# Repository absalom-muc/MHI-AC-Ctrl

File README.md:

# MHI-AC-Ctrl
Reads and writes data (e.g. power, mode, fan status etc.) from/to a Mitsubishi Heavy Industries (MHI) air conditioner (AC) via SPI controlled by MQTT. The AC is the SPI master and the ESP8266 is the SPI slave.

# Attention:
:warning: You have to open the indoor unit to have access to the SPI. Opening of the indoor unit should be done by 
a qualified professional because faulty handling may cause leakage of water, electric shock or fire! :warning: 

# Prerequisites:
For use of the program you have to connect your ESP8266 (I use a LOLIN(WEMOS) D1 R2 & mini with 80 MHz) via a
cable connector to your air conditioner. This has to be a split device (separated indoor and outdoor unit).
I assume that all AC units of the type "SRK xx ZS-S" / "SRC xx ZS-S" are supported. I use the indoor unit SRK 35 ZS-S and the outdoor unit SRC 35 ZS-S. Users reported that additionally the following models are supported:

- [SRF xx ZJX-S1](https://github.com/absalom-muc/MHI-AC-Ctrl/issues/17#issue-632187165)
- [SRF xx ZMX-S](https://github.com/absalom-muc/MHI-AC-Ctrl/issues/17#issuecomment-704789297)
- [SRF xx ZMXA-S](https://github.com/absalom-muc/MHI-AC-Ctrl/pull/91)
- SRF xx ZF-W
- [SRF xx ZS-W](https://github.com/absalom-muc/MHI-AC-Ctrl/pull/216#issue-3234769567) works with frame size 20
- [SRK xx ZJ-S](https://github.com/absalom-muc/MHI-AC-Ctrl/issues/10)
- [SRK xx ZM-S](https://github.com/absalom-muc/MHI-AC-Ctrl/issues/9)
- [SRK xx ZJX-S](https://github.com/absalom-muc/MHI-AC-Ctrl/issues/17#issuecomment-646469621)
- [SRK xx ZJX-S1](https://github.com/absalom-muc/MHI-AC-Ctrl/issues/17#issuecomment-646968940)
- [SRK xx ZR-WF](https://github.com/absalom-muc/MHI-AC-Ctrl/issues/214)
- [SRK xx ZRA-W](https://github.com/absalom-muc/MHI-AC-Ctrl/issues/17#issuecomment-730628655) / DXK xx ZRA-W
- [SRK xx ZSA-W](https://github.com/absalom-muc/MHI-AC-Ctrl/issues/17#issuecomment-891649495) / DXK xx ZSA-W
- [SRK63ZSPR-S](https://github.com/absalom-muc/MHI-AC-Ctrl/issues/149)
- SRK xx ZSXA-W/A
- [SRK xx ZSX-S](https://github.com/absalom-muc/MHI-AC-Ctrl/issues/6#issuecomment-582242372)
- [SRK xx ZSX-W](https://github.com/absalom-muc/MHI-AC-Ctrl/issues/17#issuecomment-643748095)
- [SRK xx ZS-W](https://github.com/absalom-muc/MHI-AC-Ctrl/issues/121)
- [SRK xx ZS-WF](https://github.com/absalom-muc/MHI-AC-Ctrl/issues/121#issuecomment-1938350129)
- [SRC 35Z SA-W]
- [DXK xx ZMA-S](https://github.com/absalom-muc/MHI-AC-Ctrl/issues/201)
- [SRK 2824 T (Japanese domestic model)](https://github.com/absalom-muc/MHI-AC-Ctrl/issues/211)

Unsupported models:
- [SRK71ZEA-S1](https://github.com/absalom-muc/MHI-AC-Ctrl/issues/143)
- [SRK35ZC-S](https://github.com/absalom-muc/MHI-AC-Ctrl/issues/154)
- [SRK xx ZSPR-S](https://github.com/absalom-muc/MHI-AC-Ctrl/issues/200) (except SRK63ZSPR-S)

If you find out that also other models are supported that are not listed here, please give feedback so that I can expand the list. In general, please recheck if your AC has a CNS connector before you spend time and money to build the hardware.

# Installing:

## Hardware:
The ESP8266 is powered from the AC via DC-DC (12V -> 5V) converter. 
The ESP8266 SPI signals SCL (SPI clock), MOSI (Master Out Slave In) and MISO (Master In Slave Out) are connected via a voltage level shifter 5V <-> 3.3V with the AC. Direct connection of the signals without a level shifter could damage your ESP8266!
More details are described in [Hardware.md](Hardware.md).

## Software:
The program uses the following libraries:
 - MQTT client library [PubSubClient3](https://github.com/hmueller01/pubsubclient3)
   - :warning: Don't use PubSubClient v2.8.0, it is broken due to issue [#747](https://github.com/knolleary/pubsubclient/issues/747) :warning:
 - [ArduinoOTA](https://github.com/esp8266/Arduino/tree/master/libraries/ArduinoOTA) (might be removed in future)
 
and optionally you need for the use of an external temperature sensor DS18x20 the libraries
 - [OneWire](https://www.pjrc.com/teensy/td_libs_OneWire.html)
 - [DallasTemperature](https://github.com/milesburton/Arduino-Temperature-Control-Library)

Please check the GitHub pages to see how to install them (usually via tools -> libraries).

Create a sub-directory "MHI-AC-Ctrl" and copy the files from the latest [release](https://github.com/absalom-muc/MHI-AC-Ctrl/releases) src directory in your MHI-AC-Ctrl sub-directory. You could also use the recently updated version in the [src folder](src) but with the risk that it is more unstable. The stability of the program is better when you compile it for a CPU frequency of 160MHz.
The configuration options are described in [SW-Configuration.md](SW-Configuration.md).

In a previous version (see [here](https://github.com/absalom-muc/MHI-AC-SPY)) I used the Hardware-SPI of the ESP8266. But since the SPI documentation of ESP8266 is poor, I decided to switch to a Software based SPI.
This Software based SPI is reliable and the performance of the ESP8266 is sufficient for this use case.
In case of problems please check the [Troubleshooting guide](Troubleshooting.md).

# Enhancement
If you are interested to have a deeper look on the SPI protocol or want to trace the SPI signals, please check [MHI-AC-Trace](https://github.com/absalom-muc/MHI-AC-Trace). But this is not needed for the standard user of MHI-AC-Ctrl.

# License
This project is licensed under the MIT License - see the LICENSE.md file for details

# Acknowledgments
The coding of the [SPI protocol](https://github.com/absalom-muc/MHI-AC-Trace/blob/main/SPI.md) of the AC is a nightmare. Without [rjdekker's MHI2MQTT](https://github.com/rjdekker/MHI2MQTT) I had no chance to understand the protocol! Unfortunately rjdekker is no longer active on GitHub. He used an Arduino plus an ESP8266 for his project.
Also thank you very much on the authors and contributors of [MQTT client](https://github.com/knolleary/pubsubclient), [ArduinoOTA](https://github.com/esp8266/Arduino/tree/master/libraries/ArduinoOTA), [OneWire](https://www.pjrc.com/teensy/td_libs_OneWire.html) and [DallasTemperature](https://github.com/milesburton/Arduino-Temperature-Control-Library) libraries.

Last but not least thank you for the implementation of MHI-AC-Ctrl in [different environments](https://github.com/absalom-muc/MHI-AC-Ctrl/blob/master/SW-Configuration.md#integration-examples) (FHEM, Tasmota, Home Assistant etc.)

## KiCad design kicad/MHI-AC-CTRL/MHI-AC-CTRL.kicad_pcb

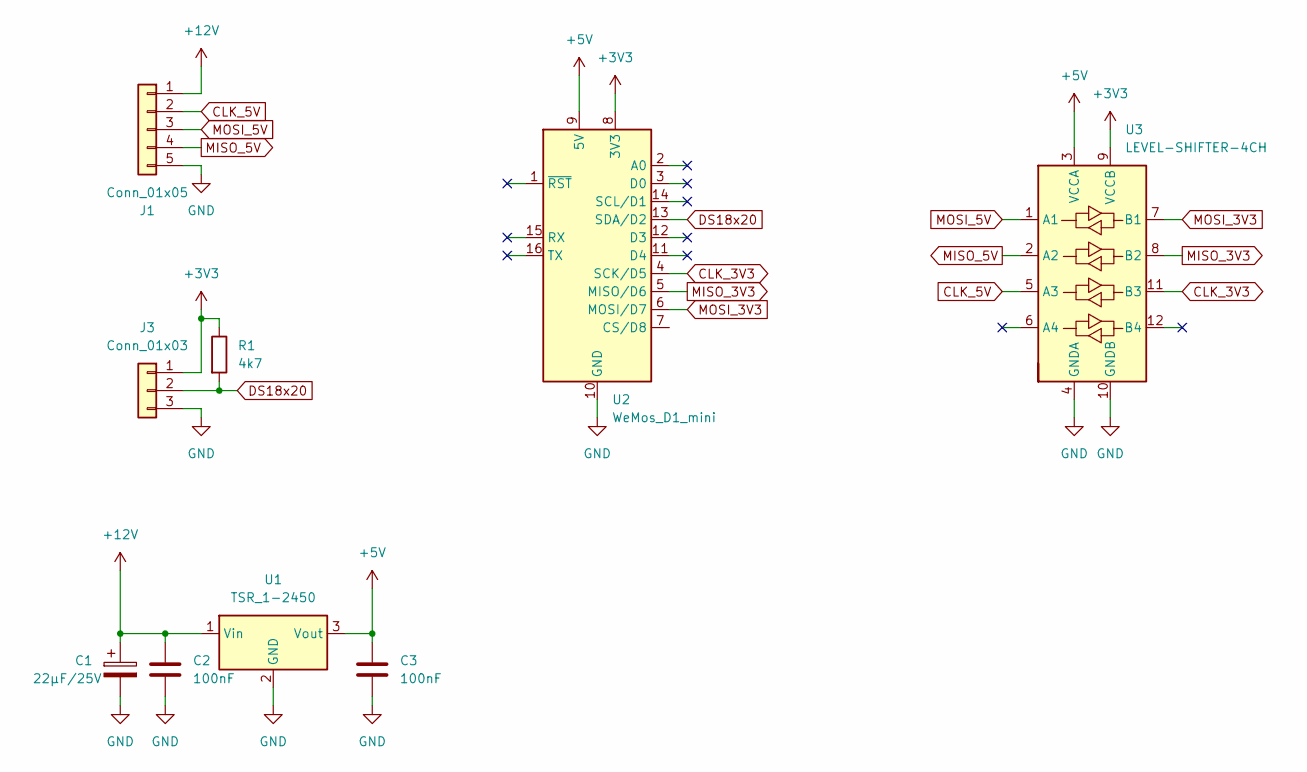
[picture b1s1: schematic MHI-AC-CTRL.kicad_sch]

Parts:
C1: 22μF/25V; CP_Axial_L10.0mm_D4.5mm_P15.00mm_Horizontal
C2, C3: 100nF; C_Disc_D3.0mm_W1.6mm_P2.50mm
J1: Conn_01x05; CONN-TH_5P-P2.50_05JQ-BT
J3: Conn_01x03; JST_XH_B3B-XH-A_1x03_P2.50mm_Vertical
R1: 4k7; R_Axial_DIN0207_L6.3mm_D2.5mm_P10.16mm_Horizontal
U1: TSR_1-2450; Converter_DCDC_TRACO_TSR-1_THT
U2: WeMos_D1_mini; WEMOS_D1_mini_light
U3: LEVEL-SHIFTER-4CH; SOIC-14_3.9x8.7mm_P1.27mm

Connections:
+3V3: J3.1, R1.1, U2.8 (3V3), U3.9 (VCCB)
+5V: C3.1, U1.3 (Vout), U2.9 (5V), U3.3 (VCCA)
+12V: C1.1, C2.1, J1.1, U1.1 (Vin)
CLK_3V3: U2.4 (SCK/D5), U3.11 (B3)
CLK_5V: J1.2, U3.5 (A3)
DS18x20: J3.2, R1.2, U2.13 (SDA/D2)
GND: C1.2, C2.2, C3.2, J1.5, J3.3, U1.2 (GND), U2.10 (GND), U3.4 (GNDA), U3.10 (GNDB)
MISO_3V3: U2.5 (MISO/D6), U3.8 (B2)
MISO_5V: J1.4, U3.2 (A2)
MOSI_3V3: U2.6 (MOSI/D7), U3.7 (B1)
MOSI_5V: J1.3, U3.1 (A1)

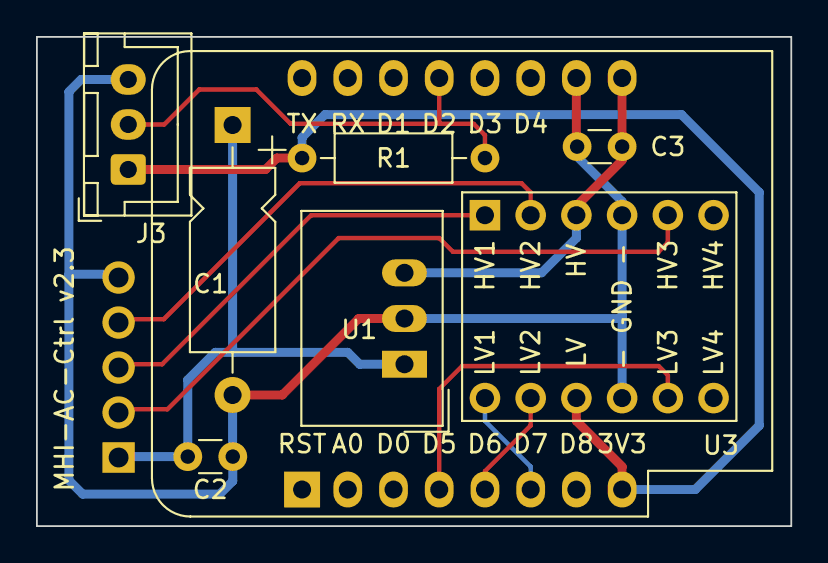
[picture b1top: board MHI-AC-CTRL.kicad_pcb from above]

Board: 2 copper layers, 41.9 x 27.2 mm, 9 parts (1 on the bottom side), 11 nets.

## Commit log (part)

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2019-12-07 Create tmp
2019-12-15 update for v1.1
    Error code (DB4) added
    OTA is now also working when waiting for a MQTT connection
2019-12-17 Vanes information enhanced
    Due to update from niclet in the thread https://github.com/rjdekker/MHI2MQTT/issues/8#issuecomment-557870093
2019-12-21 some minor corrections
    clarification related to vanes
2019-12-21 configuration images added
2019-12-21 Showing different configurations
2019-12-21 not needed here
2019-12-21 Assembled PCB figure added
2020-01-18 update v1.2
    see Version.md
2020-01-20 Figures labeled
2020-01-20 Connection between AC and remote control clarified
2020-01-27 Fix logic error on MQTT connection failure backoff
2020-03-01 typos for v1.3 corrected
2020-03-01 link for src directory added
2020-03-01 typos corrected
2020-03-01 link to SPI.md added
2020-03-06 Clarification for Vanes status
2020-04-26 Timing diagram frame & byte
2020-04-26 timing diagram and timing values added
2020-04-26 cable connection diagram added
2020-05-14 Added changeable defs for Power and Mode states
2020-05-14 Operation date mode edits
2020-05-14 Updated MQTT readme with overrides
2020-05-14 Added OTA_NAME. Added MQTT_PREFIX example
2020-05-14 Corrected power and mode syntax
2020-06-05 update to v2.0
    see Version.md
2020-06-05 format issue resolved
2020-06-06 bug in row 192 fixed (wrong interrupt handler was selected)
    and some minor code rebuild
2020-06-07 unused variables removed
2020-06-07 write to AC simplified
2020-06-07 comment added
2020-06-12 added supported AC models
2020-06-14 1.Fix the pins are not match definition 2.Support for ESP-01
2020-06-14 Fix power on randomly
2020-06-15 Remove support for ESP-01
2020-06-15 Revert because it's still broken
2020-06-15 fix of issue #18 (AC Power off randomly)
    fix of issue #18 https://github.com/absalom-muc/MHI-AC-Ctrl/issues/18#issuecomment-643739863. The illegal (dummy) value 0xff from opdata was used for MISO_DB6. This led to the shutdown of the air con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
2020-06-15 List of supported AC models enhanced, SW installation description adapted
2020-06-18 link to error code document updated
2020-06-20 supported models added
2020-06-21 Create frequency_measurement.ino
    Used for measurement of the SCK period and byte/frame period
2020-06-24 SPI logger
    logs the timing of the SPI signal edges
2020-06-24 v2.01
    - No functional changes
    - Further reduction of memory usage
    - Compiler warnings removed
    - set-mechanism reworked
    - SCK by SCK_PIN replaced according to [pull request 19](https://github.com/absalom-muc/MHI-AC-Ctrl/pull/19)
    - Shift void MeasureFrequency() from support.cpp to MHI-AC-Ctrl-core.cpp
2020-06-24 v2.01
2020-06-28 update to v2.02
    Functionality for POWERON_WHEN_CHANGING_MODE enhanced, the according #define shifted to support.h
2020-06-28 typo in HOSTNAME corrected
2020-07-01 Made warning clearer not to use PubSubClient v2.8.0
2020-07-01 switched to vcd format
    use e.g. PulseView to see the waveform
2020-07-08 reference to Troubleshooting.md added
2020-07-09 updates for 2.03
    - Functionality for POWERON_WHEN_CHANGING_MODE improved in MHI-AC-Ctrl.ino
    - WiFi mode restricted to STA (no more AP) in support.cpp
2020-07-09 info for fan auto added
2020-07-09 update to v2.1
    generation of vcd improved
2020-07-27 Another supported model
    Hi absalom, thank you very much for this project.
    I successfully installed your adapter yesterday.
    My MHI model is: **SRK 35 ZS-W**
2020-07-27 Fixing link to SERVICE SUPPORT HANDBOOK
2020-07-27 Another supported model (#35)
    Hi absalom, thank you very much for this project.
    I successfully installed your adapter yesterday.
    My MHI model is: **SRK 35 ZS-W**
2020-07-29 link related to the meaning of the operating data updated based on pull request #36
    see pull request https://github.com/absalom-muc/MHI-AC-Ctrl/pull/36
2020-07-29 important warning related to the 2-pin connector added
2020-08-09 external temperature sensor disabled per default
    according to issue 32 in https://github.com/absalom-muc/MHI-AC-Ctrl/issues/32
2020-08-28 link to Gerber files added
2020-09-07 - refactored board
2020-09-10 - updatet HW infos
2020-09-11 - add openhab documentation example
2020-09-11 - link to SW-Configuration.md
2020-09-11 invert pin 2 and 3, remove AIRWIRE from DS18x20
2020-10-07 MHI AC model added
2020-11-20 SRK xx ZRA-W added
2021-01-18 Update hrponline hint document link
    Fixed broken link
2021-01-18 Update hrponline hint document link (#52)
    Fixed broken link
2021-02-06 PCB layout update
2021-02-06 comment related to draft SW status removed
2021-04-01 link to swapped pins on PCB removed
    No longer needed due to new PCB layout
2021-04-27 Added unsupported model
    SRKxxZSPR-S doesn’t have the required connector
2021-04-28 Added unsupported model (#57)
    SRKxxZSPR-S doesn’t have the required connector
2021-05-15 added some integration examples
2021-08-30 Made WiFi SSID, hostname and MQTT server dynamic
2021-09-10 Update SW-Configuration.md
    Added integration example for ESPHome and "WiFi SSID, hostname and MQTT server dynamic"
2021-09-10 Added reference to different implementations
2021-09-28 v2.3, see Version.md
2021-11-13 update 2.5R1
    see Version.md
2021-12-17 v2.5R21
    - calculation of RETURN-AIR in MHI-AC-Ctrl.ino corrected
    - Removed the option #define ROOM_TEMP_IU for adaption by the user in support.h. Now it is generated automatically when ROOM_TEMP_DS18X20 and ROOM_TEMP_MQTT are not defined
    - Reworked WiFi network re-scan function
2021-12-18 link to MHI-AC-Trace added
    SPI.md removed here and shifted to MHI-AC-Trace repository
2022-04-14 added voltage measurement for SCK/MOSI
2022-05-24 Update README.md
    Add to supported models list
2022-05-24 Update README.md (#91)
    Add to supported models list
2022-05-29 Update issue templates
2022-06-04 Update README.md
    added SRF xx ZS-W
2022-06-07 Resolution for Tsetpoint added
2022-06-09 update to v2.5R3
    see Version.md for details
2022-06-16 reference added to discussion if the level shifter can be omitted
2022-08-28 update 2.6R2
    mainly Fan with "Auto" implemented
2022-10-25 kicad: Redo v2.2 in KiCad
    As KiCad has become quite popular (and eagle less so) offer the same
    design in KiCad going forward.
2022-10-31 kicad: Redo v2.2 in KiCad (#106)
    As KiCad has become quite popular (and eagle less so) offer the same
    design in KiCad going forward.
2022-10-31 KiCad PCB added
2022-11-03 Enhanced explanation for ROOM_TEMP_MQTT_TIMEOUT
2022-11-05 note for the KiCad PCB added
2022-11-09 kicad: Move connector to the bottom of the PCB
    This changes the appearance of the connector only! The pin-out remains
    identical, the gerbers, identical. Only the location of the connector
    moved, which causes the silkscreen to change and the 3D render.
2022-11-13 Added details of the error codes and description how to add log files
2022-12-18 Added description of ENHANCED_RESOLUTION
2022-12-20 Removed Troom_offset topic
2022-12-21 update to v2.6R3
    Added switch for Troom filtering
2022-12-21 update v2.6R4
    Added Enhance resolution of Tsetpoint
2022-12-21 Added hint that 160MHz CPU frequency should be used for compile
2022-12-22 changed TEMP_MEASURE_PERIOD to default value 0
2022-12-22 update to v2.6R5 (added ROOM_TEMP_DS18X20_OFFSET)
2022-12-23 Fixed section 'Enhance resolution of Tsetpoint'
2023-01-28 Update for 2.6 release
    see Version.md
2023-01-29 Fix for fan not showing 4 and Auto after powerdown AC
2023-02-11 Added version.md and support.h
2023-02-11 Fix for fan not showing 4 and Auto after powerdown AC (#132)
    * Fix for fan not showing 4 and Auto after powerdown AC
    * Added version.md and support.h
2023-03-04 Added Energy used in kWH
2023-03-05 Added Energy used in kWH (#135)
2023-03-05 version fixed
2023-03-26 Change MISO sending and avoid jitter
    - fix some compiler warnings by [glsf91](https://github.com/glsf91)
    - change sending MISO with faster refresh of data every 20s by [glsf91](https://github.com/glsf91)
    - avoid jitter with internal temperature sensor, now updating atmost every 5s by [glsf91](https://github.com/glsf91)
    - fix print wifi encryption type by [glsf91](https://github.com/glsf91)
    - skip not usable values for DB18B20 by [glsf91](https://github.com/glsf91)
2023-07-19 Try to get rid of room temperatures of 48,25 °C
    In my Home assistant environment, I got some random spikes of 48,25 °C, which were disturbing the charts.
2023-07-19 Accidentally removed the opening curly bracket
2023-08-05 reworked list of supported models
    added a link to each supported model to make it more comphrehensible
2023-08-28 KiCad: Fix J1 connector
    This fixes the J1 connector footprint and 3D model by using
    easyeda2kicad [0] to pull the data from LCSC!
    Closes #111
    [0]: https://github.com/uPesy/easyeda2kicad.py
2023-08-28 KiCad: Fix J1 connector (#155)
    This fixes the J1 connector footprint and 3D model by using
    easyeda2kicad [0] to pull the data from LCSC!
    Closes #111
    [0]: https://github.com/uPesy/easyeda2kicad.py
2023-09-28 Added 3D auto and vanes L/R
    Added 3D auto and vanes L/R. You have to enable this.
2023-10-02 Some cosmetic issues
2023-10-02 Resolved cosmetic issue
2023-10-23 Add SRC35ZSA-W to supported model list
    I've built and installed several of these units from the Gerber files on
    the website via JLC-PCB and have full functionality with this model.
2023-10-26 Update SW-Configuration.md
    Added description Errorcode topic
2023-10-26 Fix link
2023-11-27 Added HA in SW-Configuration.md
2023-11-28 Correct J1 connector pinout
    Fixes #167
    Regenerated PDF and gerber/drill
2024-01-08 Correct J1 connector pinout (#168)
    Fixes #167
    Regenerated PDF and gerber/drill
2024-01-12 Update SW-Configuration.md
    Added Display AC controller to integration list
2024-01-15 Update SW-Configuration.md. Replaced MQTT Errorcode topic
    Changed MQTT Errorcode topic to MQTT operating data PROTECTION-NO topic because of wrong description.
2024-02-07 git: Enable LFS for PDF files
    No need to track datasheets.
2024-02-08 remove: Drop generateable files
    Delete generatable files, as we should just generate them from a pipeline.
    In addition, the pdf makes it impossible to enable git lfs for binary files.
2024-02-12 Add info on compatibility with SRK xx ZS-WF models.
2024-02-12 Added SRK xx ZS-WF to supported models
2024-04-13 Added SRK 25 ZSPR-S to unsupported list
2024-05-31 Add alternate supported model numbers in README
    SRK and DXK are the same in the ZRA-W/ZSA-W series.
2024-06-15 Added link to esp32 variant in Hardware.md
2024-08-28 Fork off hardware to seperate repo
    It is increasingly becoming more difficult to keep track of hardware and
    software changes. E.g. git-tags refer to software, but the hardware also
    has versions.
    To reduce the scope of this repository, and make things cleaner
    repository wise, lets split off these two repositories into software and
    hardware.
2024-08-30 Update Hardware.md Kicad
2024-11-06 changed SRK63ZSPR-S supported and SRK xx ZSPR-S unsupported
2024-11-14 Added DXKxxZMA-S as supported
2025-03-06 Fix emoji warning
2025-03-26 Add note about loss of timer functionality in troubleshooting
2025-03-26 Rephrase note about loss of timer functionality
2025-06-16 docs: move from unmaintained knolleary/pubsubclient to hmueller01/pubsubclient3
2025-07-03 AddedMHI SRKxxZR-WF
2025-07-16 Add support for SRF xx ZS-W series to the readme
2025-11-19 Update README.md
    path to pull request added
2025-11-19 Add validated support for SRF xx ZS-W series to the readme (#216)
    * Add support for SRF xx ZS-W series to the readme
    * Update README.md
    path to pull request added
    ---------
2025-11-19 docs: move from unmaintained knolleary/pubsubclient to hmueller01/pubsubclient3 (#212)
